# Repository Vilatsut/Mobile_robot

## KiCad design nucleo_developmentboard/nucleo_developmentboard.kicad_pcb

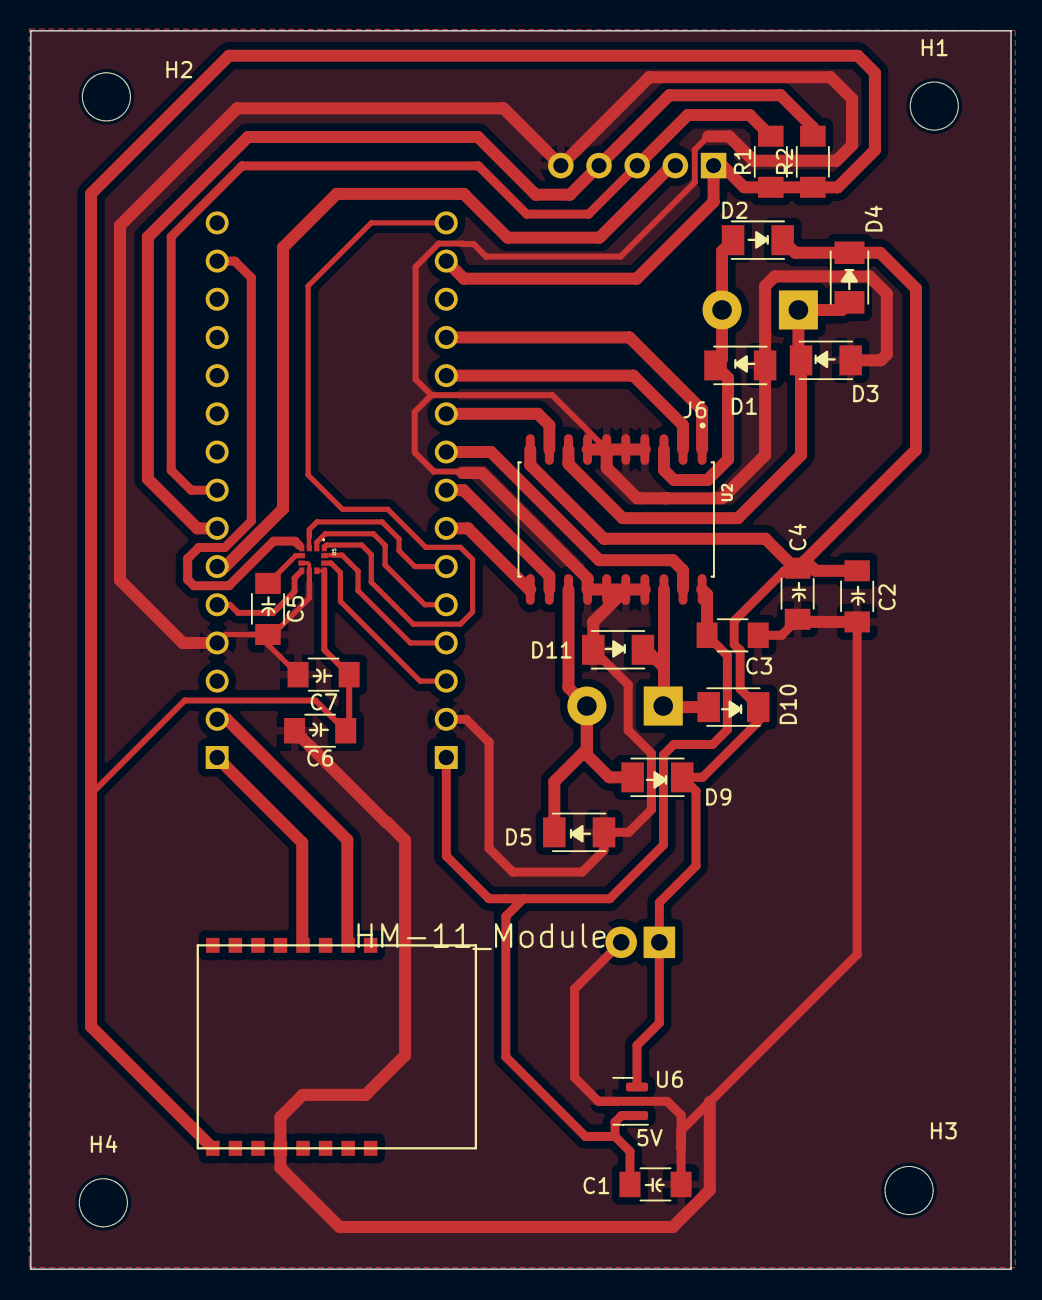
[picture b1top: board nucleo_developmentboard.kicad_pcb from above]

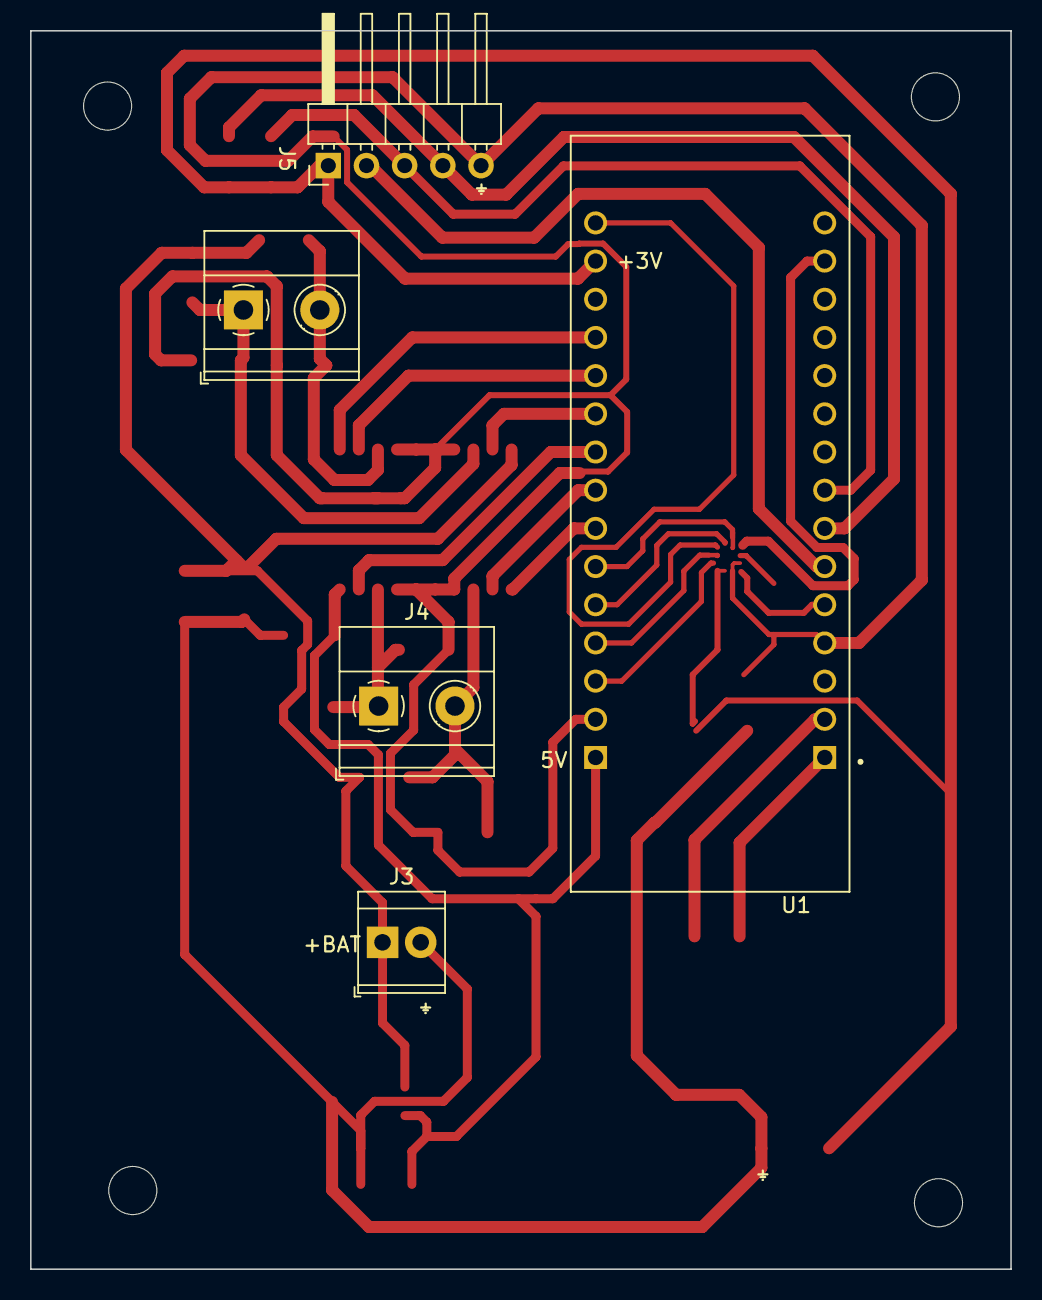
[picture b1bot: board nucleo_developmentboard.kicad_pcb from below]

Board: 2 copper layers, 65.2 x 82.4 mm, 30 parts (5 on the bottom side), 27 nets.

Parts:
C1, C2, C3, C4, C7: 10uF; C_1206
C5, C6: 100nF; C_1206
D1, D2, D3, D4, D5, D9, D10, D11: Diode_Schottky_MiniSMA; SOD-123T
H1, H2, H3, H4: MountingHole; MountingHole_3.2mm_M3_ISO7380
J3: Conn_01x02_Socket; TerminalBlock_TE_282834-2_1x02_P2.54mm_Horizontal
J4, J6: MOTOR2 OUT; TerminalBlock_Phoenix_MKDS-1,5-2-5.08_1x02_P5.08mm_Horizont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
J5: LIDAR_conn; PinHeader_1x05_P2.54mm_Horizontal
R1: 1k; R_1206
R2: 1K; R_1206
U1: NUCLEO-L432KC; mod
U2: L293DD; SOIC127P1032X265-20N
U4: HM-11_Module
U5: LSM303CTR; LGA12R50P_200X200X100
U6: LM3480-5.0; SOT-23

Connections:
3V3: C6.1, C7.1, J5.1, R1.1, R2.1, U1.CN4_14 (+3V3), U4.9 (3V3), U5.9 (VDD), U5.10 (VDD_IO)
+BAT: C2.1, C4.1, D2.1 (K), D4.1 (K), D9.1 (K), D10.1 (K), J3.1, U2.10 (VS), U6.2 (VI)
A_H: U1.CN4_11 (PA1), U2.2 (INPUT_1)
A_L: U1.CN4_10 (PA3), U2.9 (INPUT_2)
B_H: U1.CN4_8 (PA5), U2.12 (INPUT_3)
B_L: U1.CN4_9 (PA4), U2.19 (INPUT_4)
DRDY: U1.CN4_3 (NRST_CN4), U5.11 (DRDY_MAG)
EN_A: U1.CN4_12 (PA0), U2.1 (ENABLE_1)
EN_B: U1.CN4_7 (PA6), U2.11 (ENABLE_2)
GND: C1.2, C2.2, C3.2, C4.2, C5.2, C6.2, C7.2, D1.2 (A), D3.2 (A), D5.2 (A), D11.2 (A), J3.2, J5.5, U1.CN3_4 (GND_CN3), U1.CN4_2 (GND_CN4), U2.4 (GND), U2.5 (GND), U2.6 (GND), U2.7 (GND), U2.14 (GND), U2.15 (GND), U2.16 (GND), U2.17 (GND), U4.12 (GND), U5.6 (GND), U5.8 (GND), U6.3 (GND)
INT_MAG: U1.CN3_5 (PA12), U5.7 (INT_MAG)
INT_XL: U1.CN4_4 (+5V), U5.12 (INT_XL)
unnamed: D1.1 (K), D2.2 (A), J6.2, U2.3 (OUTPUT_1)
unnamed: D3.1 (K), D4.2 (A), J6.1, U2.8 (OUTPUT_2)
unnamed: D5.1 (K), D9.2 (A), J4.2, U2.13 (OUTPUT_3)
unnamed: D10.2 (A), D11.1 (K), J4.1, U2.18 (OUTPUT_4)
unnamed: C5.1, U5.5 (C1)
RX: U1.CN3_2 (PA10), U4.2 (TX)
SCL: J5.3, R1.2, U1.CN3_8 (PB6)
SCLK: U1.CN4_15 (PB3), U5.1 (SCL/SPC)
SDA: J5.4, R2.2, U1.CN3_7 (PB7)
SDOI: U1.CN3_14 (PB5), U5.4 (SDA/SDI/SDO)
SMAG: U1.CN4_6 (PA7), U5.3 (CS_MAG)
SXL: U1.CN4_5 (PA2), U5.2 (CS_XL)
TX: U1.CN3_1 (PA9), U4.4 (RX)
VCC: C1.1, C3.1, U1.CN4_1 (VIN), U2.20 (VSS), U6.1 (VO)
XSHUT: J5.2, U1.CN3_6 (PB0)

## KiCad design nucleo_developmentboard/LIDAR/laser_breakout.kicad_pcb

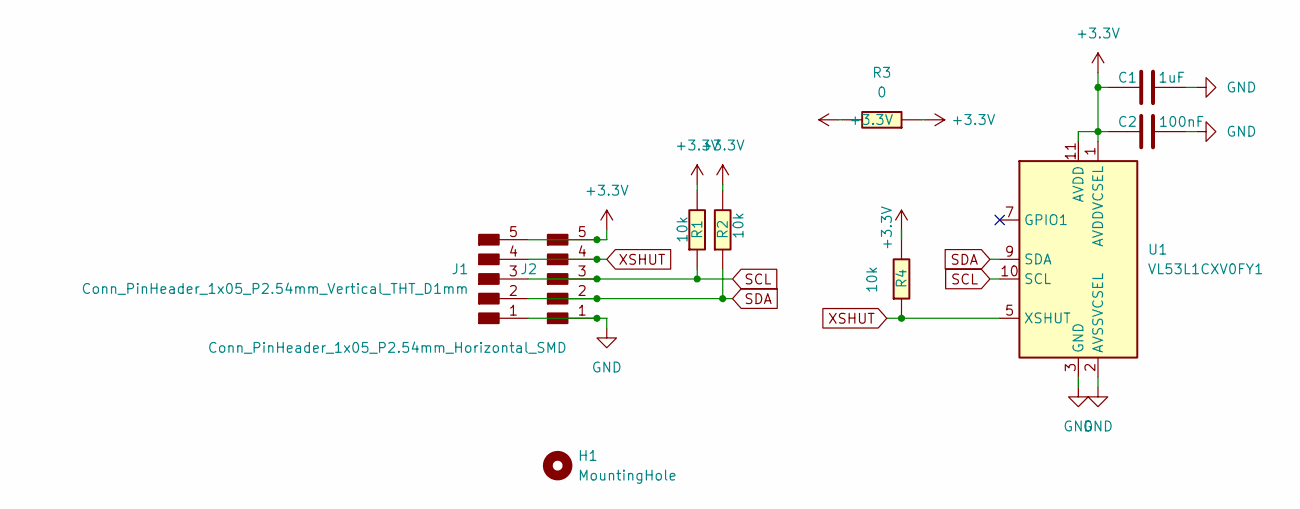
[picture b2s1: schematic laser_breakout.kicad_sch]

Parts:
C1: 1uF; C_1206
C2: 100nF; C_1206
H1: MountingHole; MountingHole_3.2mm_M3_ISO7380
J1: Conn_PinHeader_1x05_P2.54mm_Vertical_THT_D1mm; PinHeader_1x05_P2.54mm_Vertical_THT_D1mm
J2: Conn_PinHeader_1x05_P2.54mm_Horizontal_SMD; PinHeader_1x05_P2.54mm_Horizontal_SMD
R1, R2, R4: 10k; R_1206
R3: 0; R_1206
U1: VL53L1CXV0FY1; ST_VL53L1x

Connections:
+3V3: C1.1, C2.1, J1.5, J2.5, R1.1, R2.1, R3.1, R3.2, R4.1, U1.1 (AVDDVCSEL), U1.11 (AVDD)
GND: C1.2, C2.2, J1.1, J2.1, U1.2 (AVSSVCSEL), U1.3 (GND), U1.4 (GND), U1.6 (GND), U1.12 (GND)
SCL: J1.3, J2.3, R1.2, U1.10 (SCL)
SDA: J1.2, J2.2, R2.2, U1.9 (SDA)
XSHUT: J1.4, J2.4, R4.2, U1.5 (XSHUT)

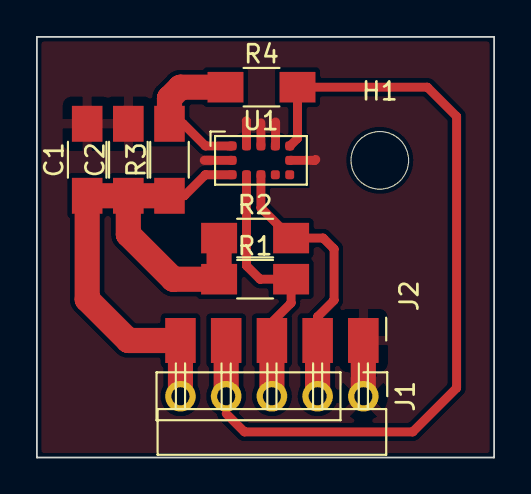
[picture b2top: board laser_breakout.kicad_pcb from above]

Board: 2 copper layers, 25.4 x 23.4 mm, 10 parts (0 on the bottom side), 5 nets.

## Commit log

2023-07-13 Added nucleo-development-board module
2023-07-13 Added nucleo-development-board module2 del backups
2023-07-22 updated Nucleo connections and switched to HM11 smd
2023-07-31 Final Nucleo board updated with all SMD components
2023-08-10 added LSM303CTR
2023-08-15 Added polarities to components
